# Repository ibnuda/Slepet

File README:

Slepet

a shameless clone of omkbd's SectorC.

firmware: https://github.com/ibnuda/qmk_firmware/tree/sixtimesseven/keyboards/slepet

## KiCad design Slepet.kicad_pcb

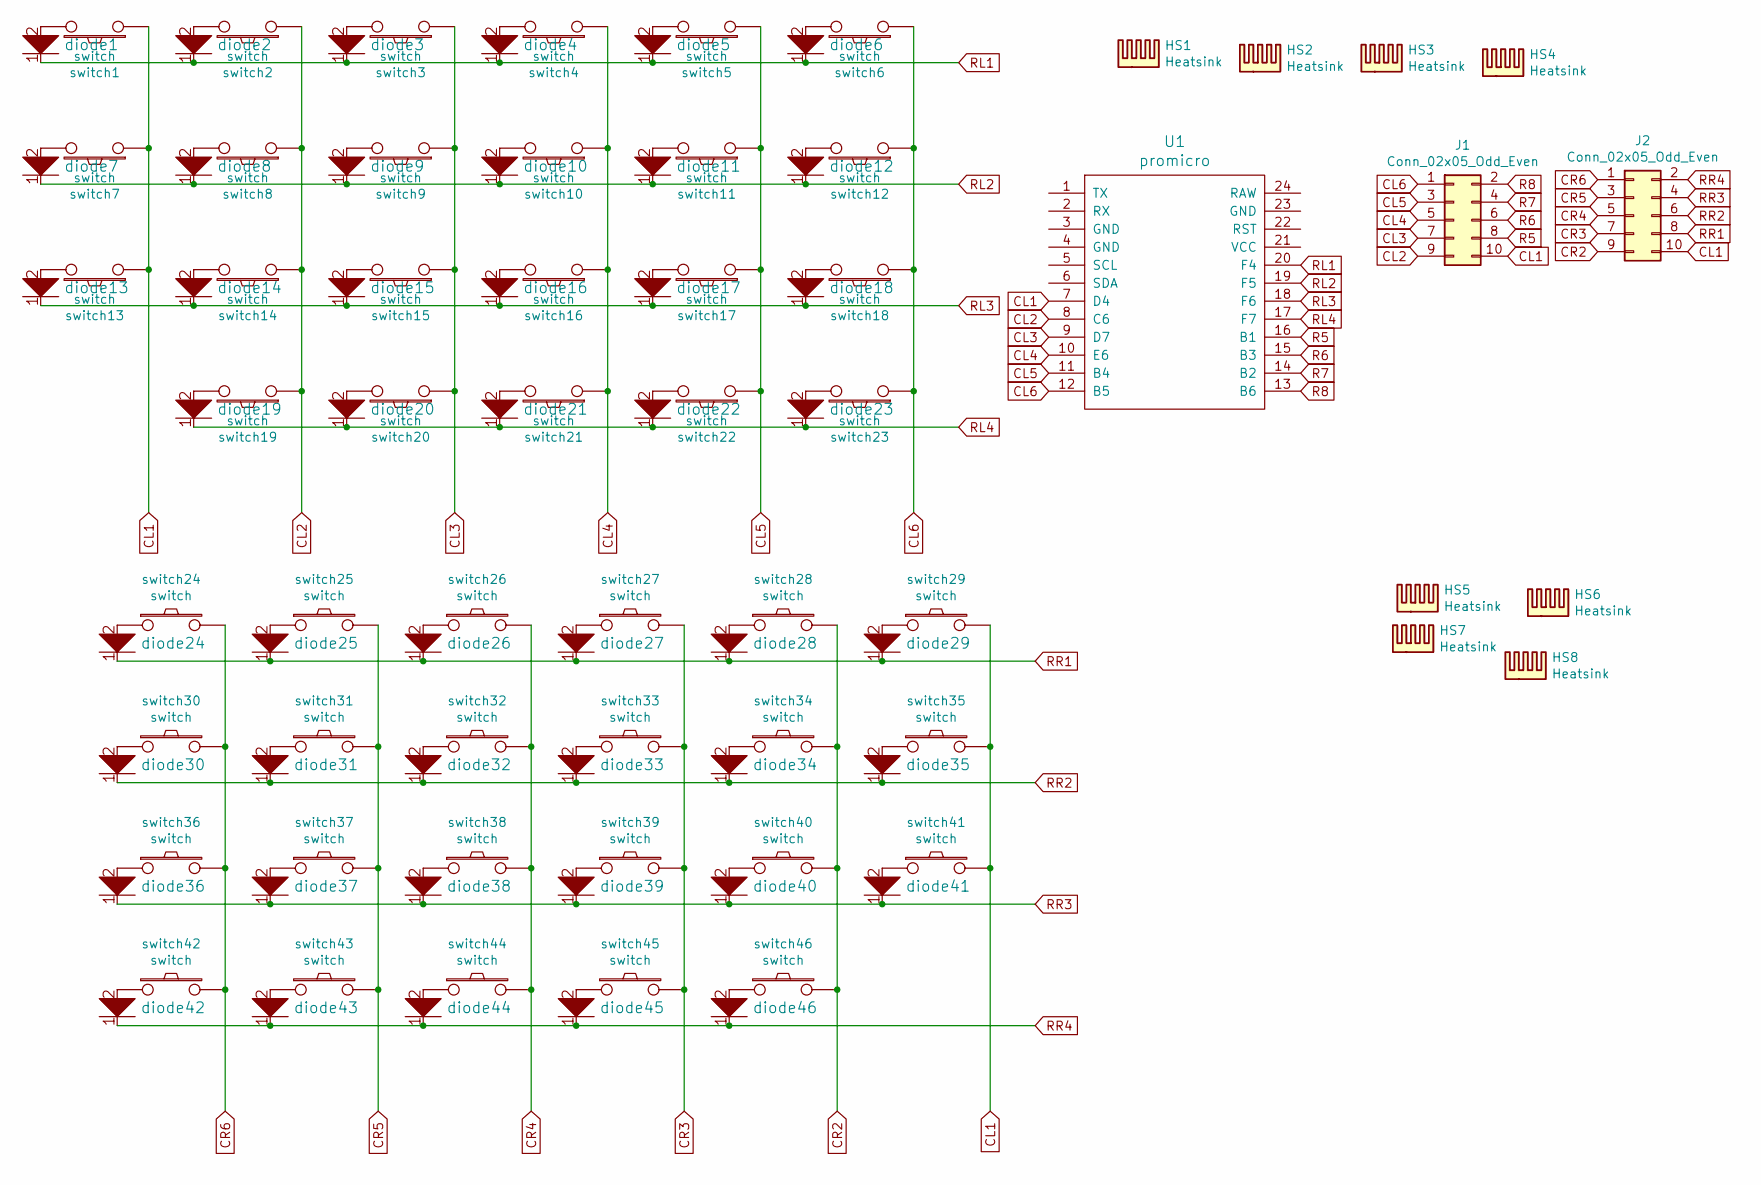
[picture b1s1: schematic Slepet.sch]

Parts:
HS1, HS2, HS3, HS4: Heatsink; baldy_luv_u
HS5, HS6, HS7, HS8: Heatsink; hole-three
J1, J2: Conn_02x05_Odd_Even; connector-shrouded
U1: promicro
diode1, diode2, diode3, diode4, diode5, diode6, diode7, diode8, diode9, diode10, diode11, diode12, diode13, diode14, diode15, diode16, diode17, diode18, diode19, diode20, diode21, diode22, diode23, diode24, diode25, diode26, diode27, diode28, diode29, diode30, diode31, diode32, diode33, diode34, diode35, diode36, diode37, diode38, diode39, diode40, diode41, diode42, diode43, diode44, diode45, diode46: diode
switch1, switch2, switch3, switch4, switch5, switch6, switch7, switch8, switch9, switch10, switch11, switch12, switch13, switch14, switch15, switch16, switch17, switch18, switch19, switch20, switch21, switch22, switch23, switch24, switch25, switch26, switch27, switch28, switch29, switch30, switch31, switch32, switch33, switch34, switch35, switch36, switch37, switch38, switch39, switch40, switch41, switch42, switch43, switch44, switch45, switch46: switch; 100-minimal-no-3d

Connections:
CL1: J1.10, J2.10, U1.7 (D4), switch1.1, switch7.1, switch13.1, switch29.2, switch35.2, switch41.2
CL2: J1.9, U1.8 (C6), switch2.1, switch8.1, switch14.1, switch19.1
CL3: J1.7, U1.9 (D7), switch3.1, switch9.1, switch15.1, switch20.1
CL4: J1.5, U1.10 (E6), switch4.1, switch10.1, switch16.1, switch21.1
CL5: J1.3, U1.11 (B4), switch5.1, switch11.1, switch17.1, switch22.1
CL6: J1.1, U1.12 (B5), switch6.1, switch12.1, switch18.1, switch23.1
CR2: J2.9, switch28.2, switch34.2, switch40.2, switch46.2
CR3: J2.7, switch27.2, switch33.2, switch39.2, switch45.2
CR4: J2.5, switch26.2, switch32.2, switch38.2, switch44.2
CR5: J2.3, switch25.2, switch31.2, switch37.2, switch43.2
CR6: J2.1, switch24.2, switch30.2, switch36.2, switch42.2
unnamed: diode1.2, switch1.2
unnamed: diode2.2, switch2.2
unnamed: diode3.2, switch3.2
unnamed: diode4.2, switch4.2
unnamed: diode5.2, switch5.2
unnamed: diode6.2, switch6.2
unnamed: diode7.2, switch7.2
unnamed: diode8.2, switch8.2
unnamed: diode9.2, switch9.2
unnamed: diode10.2, switch10.2
unnamed: diode11.2, switch11.2
unnamed: diode12.2, switch12.2
unnamed: diode13.2, switch13.2
unnamed: diode14.2, switch14.2
unnamed: diode15.2, switch15.2
unnamed: diode16.2, switch16.2
unnamed: diode17.2, switch17.2
unnamed: diode18.2, switch18.2
unnamed: diode19.2, switch19.2
unnamed: diode20.2, switch20.2
unnamed: diode21.2, switch21.2
unnamed: diode22.2, switch22.2
unnamed: diode23.2, switch23.2
unnamed: diode24.2, switch24.1
unnamed: diode25.2, switch25.1
unnamed: diode26.2, switch26.1
unnamed: diode27.2, switch27.1
unnamed: diode28.2, switch28.1
unnamed: diode29.2, switch29.1
unnamed: diode30.2, switch30.1
unnamed: diode31.2, switch31.1
unnamed: diode32.2, switch32.1
unnamed: diode33.2, switch33.1
unnamed: diode34.2, switch34.1
unnamed: diode35.2, switch35.1
unnamed: diode36.2, switch36.1
unnamed: diode37.2, switch37.1
unnamed: diode38.2, switch38.1
unnamed: diode39.2, switch39.1
unnamed: diode40.2, switch40.1
unnamed: diode41.2, switch41.1
unnamed: diode42.2, switch42.1
unnamed: diode43.2, switch43.1
unnamed: diode44.2, switch44.1
unnamed: diode45.2, switch45.1
unnamed: diode46.2, switch46.1
R5: J1.8, U1.16 (B1)
R6: J1.6, U1.15 (B3)
R7: J1.4, U1.14 (B2)
R8: J1.2, U1.13 (B6)
RL1: U1.20 (F4), diode1.1, diode2.1, diode3.1, diode4.1, diode5.1, diode6.1
RL2: U1.19 (F5), diode7.1, diode8.1, diode9.1, diode10.1, diode11.1, diode12.1
RL3: U1.18 (F6), diode13.1, diode14.1, diode15.1, diode16.1, diode17.1, diode18.1
RL4: U1.17 (F7), diode19.1, diode20.1, diode21.1, diode22.1, diode23.1
RR1: J2.8, diode24.1, diode25.1, diode26.1, diode27.1, diode28.1, diode29.1
RR2: J2.6, diode30.1, diode31.1, diode32.1, diode33.1, diode34.1, diode35.1
RR3: J2.4, diode36.1, diode37.1, diode38.1, diode39.1, diode40.1, diode41.1
RR4: J2.2, diode42.1, diode43.1, diode44.1, diode45.1, diode46.1

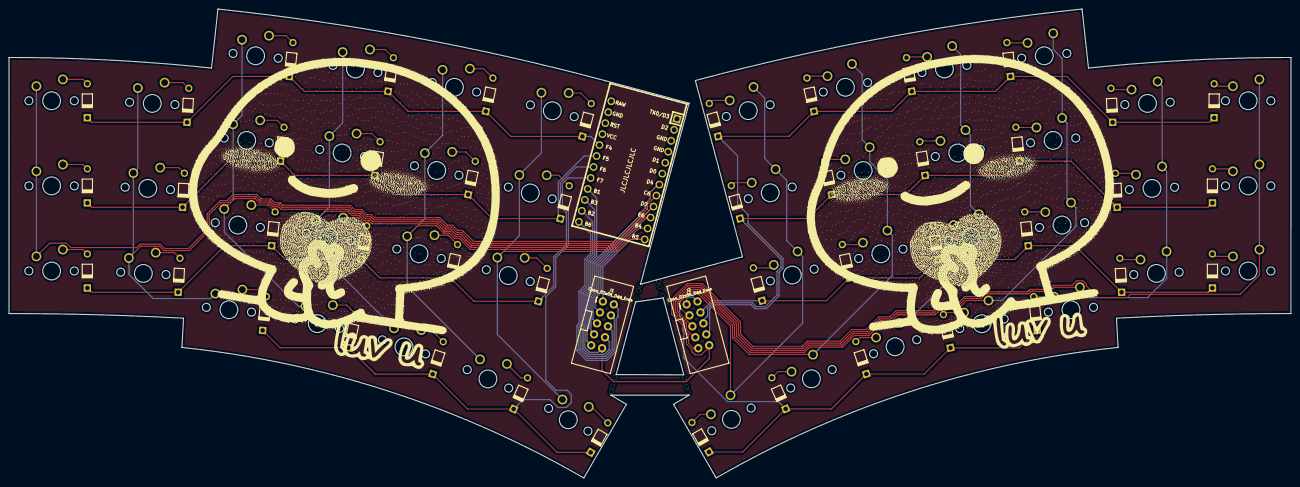
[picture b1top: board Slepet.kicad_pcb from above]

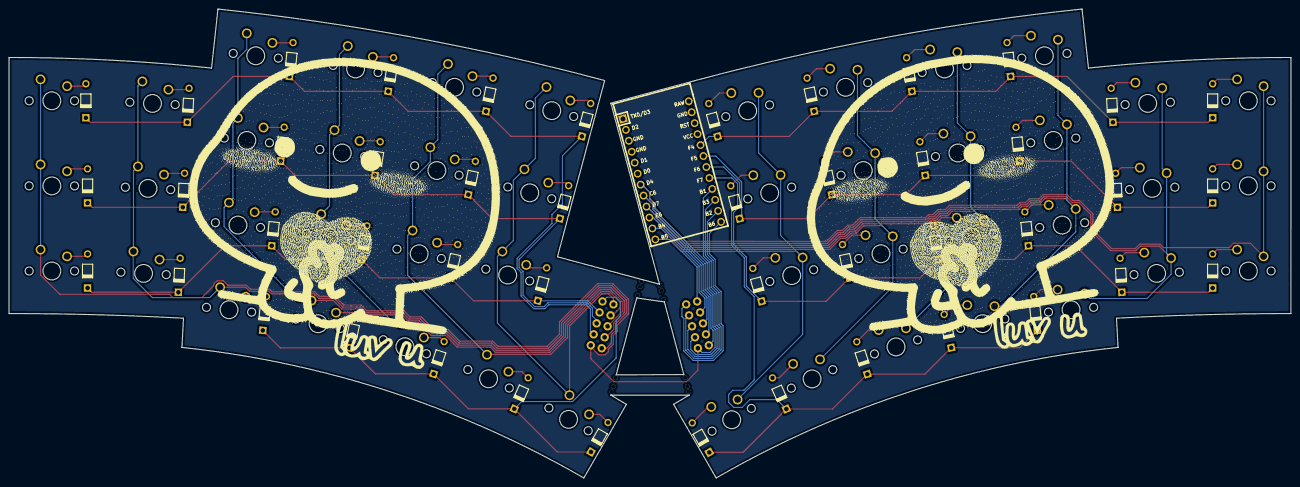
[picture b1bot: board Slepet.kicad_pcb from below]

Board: 2 copper layers, 286.9 x 105.0 mm, 103 parts (3 on the bottom side), 69 nets.

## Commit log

2021-06-03 init commit. left side should be fine.
2021-06-11 sneaky
2021-06-12 to lessen the burden.
2021-06-15 cough cough cough.
2021-06-26 add link to firmware
2021-06-28 plate
2021-06-29 3d case.
